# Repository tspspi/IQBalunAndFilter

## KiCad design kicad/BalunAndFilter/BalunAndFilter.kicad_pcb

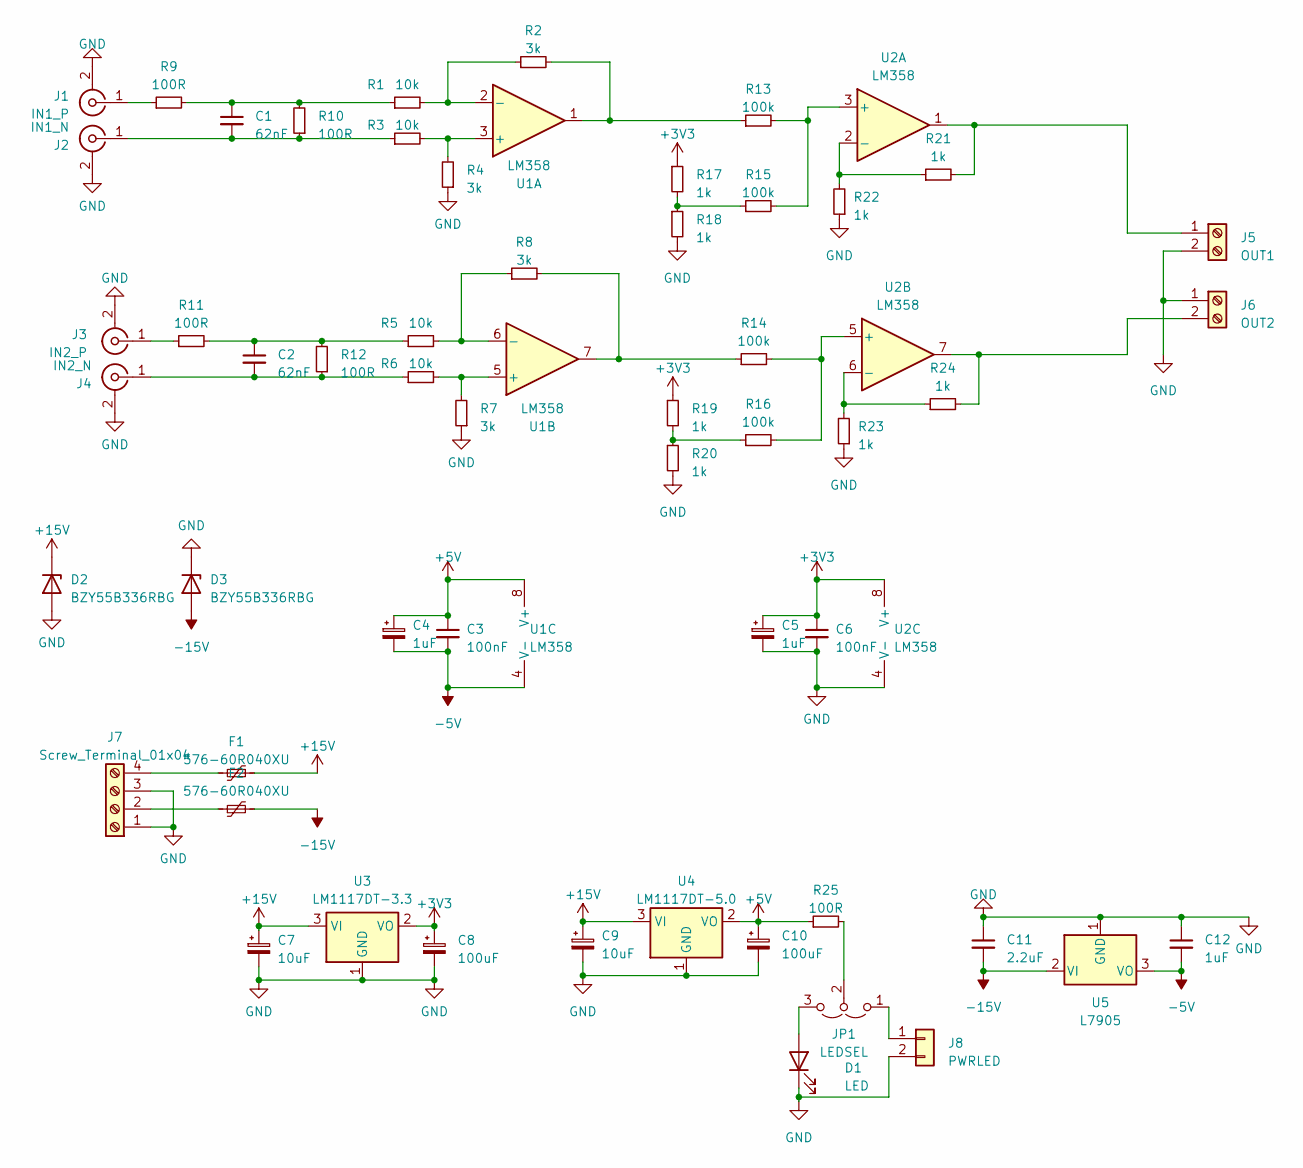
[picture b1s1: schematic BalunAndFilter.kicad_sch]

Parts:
C1, C2: 62nF; C_0805_2012Metric
C3, C6: 100nF; C_0805_2012Metric
C4, C5: 1uF; C_0805_2012Metric
C7, C9: 10uF; CP_Radial_D5.0mm_P2.50mm
C8, C10: 100uF; CP_Radial_D5.0mm_P2.50mm
C11: 2.2uF; CP_Radial_D5.0mm_P2.50mm
C12: 1uF; CP_Radial_D5.0mm_P2.50mm
D1: LED; LED_0805_2012Metric
D2, D3: BZY55B336RBG; D_DO-41_SOD81_P12.70mm_Horizontal
F1, F2: 576-60R040XU; C_Disc_D5.1mm_W3.2mm_P5.00mm
J1: IN1_P; SMA_Amphenol_901-143_Horizontal
J2: IN1_N; SMA_Amphenol_901-143_Horizontal
J3: IN2_P; SMA_Amphenol_901-143_Horizontal
J4: IN2_N; SMA_Amphenol_901-143_Horizontal
J5: OUT1; PinHeader_1x02_P2.54mm_Vertical
J6: OUT2; PinHeader_1x02_P2.54mm_Vertical
J7: Screw_Terminal_01x04; PinHeader_1x04_P2.54mm_Vertical
J8: PWRLED; PinHeader_1x02_P2.54mm_Vertical
JP1: LEDSEL; PinHeader_1x03_P2.54mm_Vertical
R1, R3, R5, R6: 10k; R_0805_2012Metric
R2, R4, R7, R8: 3k; R_0805_2012Metric
R9, R10, R11, R12, R25: 100R; R_0805_2012Metric
R13, R14, R15, R16: 100k; R_0805_2012Metric
R17, R18, R19, R20, R21, R22, R23, R24: 1k; R_0805_2012Metric
U1, U2: LM358; DIP-8_W10.16mm
U3: LM1117DT-3.3; TO-252-3_TabPin2
U4: LM1117DT-5.0; TO-252-3_TabPin2
U5: L7905; TO-220-3_Vertical

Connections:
+3V3: C5.1, C6.1, C8.1, R17.1, R19.1, U2.8 (V+), U3.2 (VO)
+5V: C3.1, C4.1, C10.1, R25.1, U1.8 (V+), U4.2 (VO)
+15V: C7.1, C9.1, D2.1 (K), F1.1, U3.3 (VI), U4.3 (VI)
-5V: C3.2, C4.2, C12.2, U1.4 (V-), U5.3 (VO)
-15V: C11.2, D3.2 (A), F2.2, U5.2 (VI)
GND: C5.2, C6.2, C7.2, C8.2, C9.2, C10.2, C11.1, C12.1, D1.1 (K), D2.2 (A), D3.1 (K), J1.2 (Ext), J2.2 (Ext), J3.2 (Ext), J4.2 (Ext), J5.2, J6.1, J7.1, J7.3, J8.2, R4.1, R7.1, R18.2, R20.2, R22.1, R23.1, U2.4 (V-), U3.1 (GND), U4.1 (GND), U5.1 (GND)
unnamed: C1.1, R1.1, R9.2, R10.2
unnamed: C2.1, R5.1, R11.2, R12.2
unnamed: D1.2 (A), JP1.3 (B)
unnamed: J1.1 (In), R9.1
unnamed: C1.2, J2.1 (In), R3.1, R10.1
unnamed: J3.1 (In), R11.1
unnamed: C2.2, J4.1 (In), R6.1, R12.1
unnamed: J5.1, R21.2, U2.1
unnamed: J6.2, R24.2, U2.7
unnamed: F2.1, J7.2
unnamed: F1.2, J7.4
unnamed: J8.1, JP1.1 (A)
unnamed: JP1.2 (C), R25.2
unnamed: R2.2, R13.1, U1.1
unnamed: R8.2, R14.1, U1.7
unnamed: R15.1, R17.2, R18.1
unnamed: R16.1, R19.2, R20.1
unnamed: R3.2, R4.2, U1.3 (+)
unnamed: R1.2, R2.1, U1.2 (-)
unnamed: R6.2, R7.2, U1.5 (+)
unnamed: R5.2, R8.1, U1.6 (-)
unnamed: R13.2, R15.2, U2.3 (+)
unnamed: R21.1, R22.2, U2.2 (-)
unnamed: R14.2, R16.2, U2.5 (+)
unnamed: R23.2, R24.1, U2.6 (-)

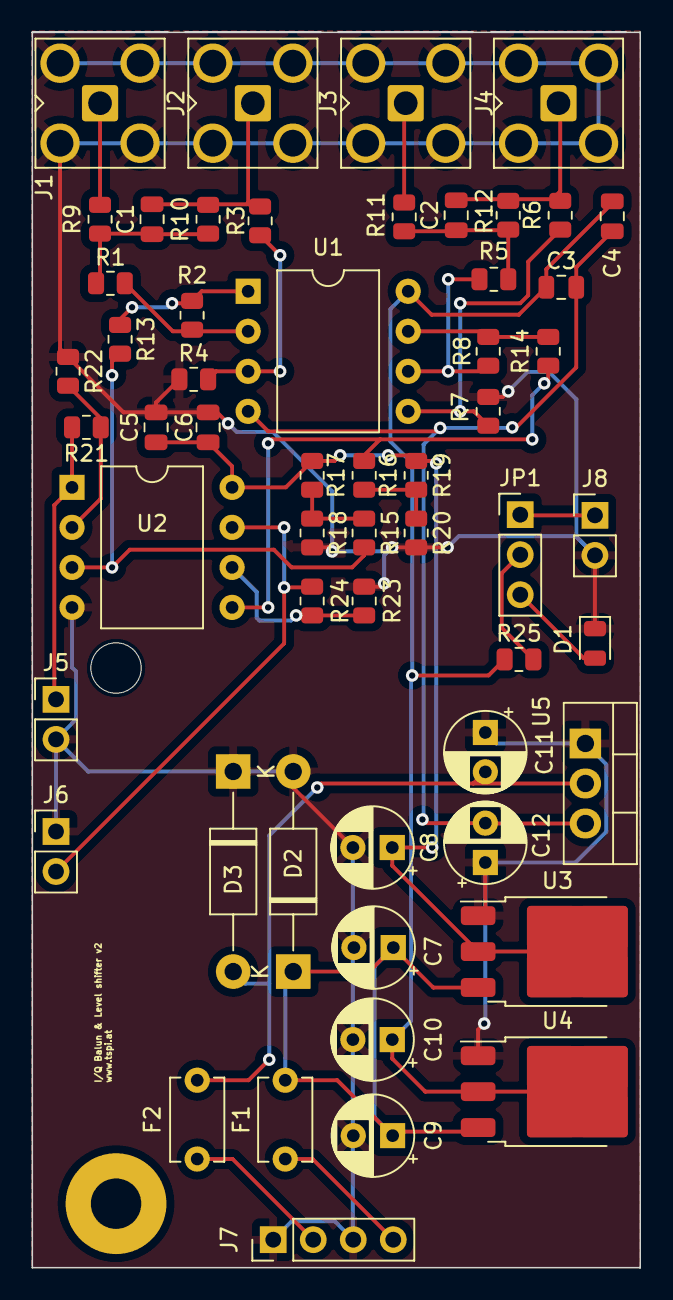
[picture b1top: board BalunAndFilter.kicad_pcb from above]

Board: 2 copper layers, 38.6 x 78.4 mm, 56 parts (0 on the bottom side), 31 nets.
